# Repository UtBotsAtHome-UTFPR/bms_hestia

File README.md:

# Battery Management System Intelligent (BMSi) 
The BMSi is a open source smart battery management system with the goal of being reliable and affordable with the ability to communicate over USB with robotic systems using ROS or computer with serial terminal, providing all the valuable data needed about the battery.

With the goal of affordability and ease o use the main component is an ESP32, using Arduino Language (C++). The complex part of this project (BQ76942) was simplified with the development of a library, and further development will be done on this to achieve full abstraction on the configuration and use of this IC, making it even more simple to use.

The hardware designs are found under [BMSi-Hardware](https://github.com/MrSerafim/BMSi-Hardware).

Updates require matching firmware and board versions!

### Copyright notice:
Some parts of this software may contain third party libraries and source code licensed under different terms.
The license applying to these files is found in the header of the file.
For all other parts the LICENSE file applies.

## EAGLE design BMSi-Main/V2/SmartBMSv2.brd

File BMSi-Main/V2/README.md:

### BMSi V2 board
This was the first released and working board.

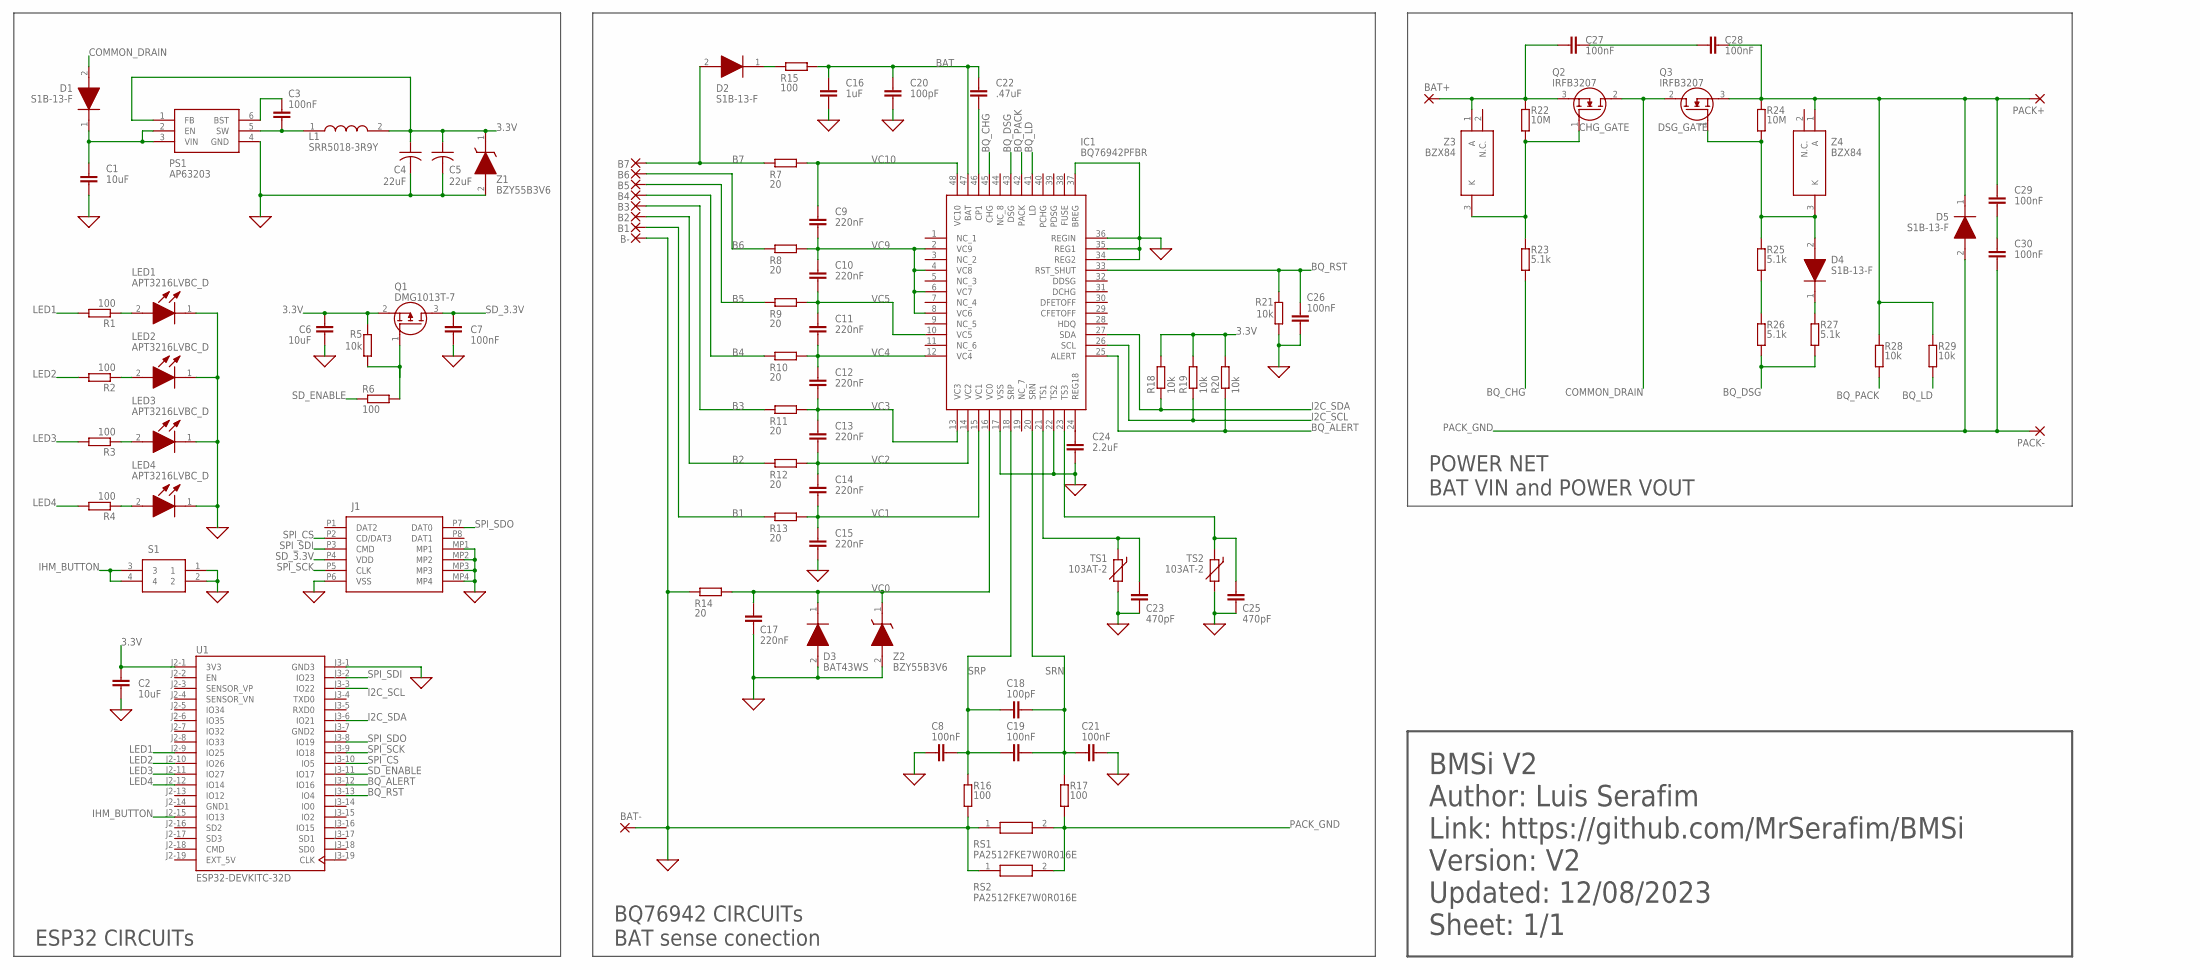
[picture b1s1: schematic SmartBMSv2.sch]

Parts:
B1, B2, B3, B4, B5, B6, B7: SMD5; SMD2,54-5,08
B-: SMD5; SMD2,54-5,08
BAT+: SMD5X10; SMD5-10
BAT-: SMD5X10; SMD5-10
C1, C2, C6: 10uF; C0805
C3, C7, C8, C19, C21, C26, C27, C28, C29, C30: 100nF; C0805
C4, C5: 22uF; C0805
C9, C10, C11, C12, C13, C14, C15, C17: 220nF; C0805
C16: 1uF; C0805
C18, C20: 100pF; C0805
C22: .47uF; C0805
C23, C25: 470pF; C0805
C24: 2.2uF; C0805
D1, D2, D4, D5: S1B-13-F; DIONM5126X230N
D3: BAT43WS; SOD2713X115N
IC1: BQ76942PFBR; QFP50P900X900X120-48N
J1: MEM2067-02-180-00-A; MEM20670218000A
L1: SRR5018-3R9Y; SRR50183R9Y
LED1, LED2, LED3, LED4: APT3216LVBC_D; LEDC3216X95N
PACK+: SMD5X10; SMD5-10
PACK-: SMD5X10; SMD5-10
PS1: AP63203; SOT95P280X100-6N
Q1: DMG1013T-7; SOT50P160X90-3N
Q2, Q3: IRFB3207; TO220_HORIZONTAL
R1, R2, R3, R4, R6, R15, R16, R17: 100; R0805
R5, R18, R19, R20, R21, R28, R29: 10k; R0805
R7, R8, R9, R10, R11, R12, R13, R14: 20; R0805
R22, R24: 10M; R0805
R23, R25, R26, R27: 5.1k; R0805
RS1, RS2: PA2512FKE7W0R016E; RESC6432X88N
S1: FSM2JSMAATR; FSM2J_1
TS1, TS2: 103AT-2; RS-2,5
U1: ESP32-DEVKITC-32D; MODULE_ESP32-DEVKITC-32D
Z1, Z2: BZY55B3V6; DIOC2012X85N
Z3, Z4: BZX84; SOT95P230X110-3N

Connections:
0: B-.1, BAT-.1, C1.2, C2.2, C4.2, C5.2, C6.1, C7.1, C8.1, C15.2, C16.2, C17.2, C20.2, C21.2, C23.2, C24.2, C25.2, C26.2, D3.2 (A), IC1.17 (VSS), IC1.22 (TS2), IC1.34 (REG2), IC1.35 (REG1), IC1.36 (REGIN), IC1.37 (BREG), J1.MP1, J1.MP2, J1.MP3, J1.MP4, J1.P6 (VSS), LED1.1 (K), LED2.1 (K), LED3.1 (K), LED4.1 (K), PS1.4 (GND), R14.1, R16.1, R21.1, RS1.1, RS2.1, S1.1, S1.2, TS1.2, TS2.2, U1.J3-1 (GND3), Z1.2 (A), Z2.2 (A)
3.3V: C2.1, C4.1, C5.1, C6.2, L1.2, PS1.1 (FB), Q1.2 (S), R5.2, R18.2, R19.2, R20.2, U1.J2-1 (3V3), Z1.1 (K)
B1: B1.1, R13.1
B2: B2.1, R12.1
B3: B3.1, R11.1
B4: B4.1, R10.1
B5: B5.1, R9.1
B6: B6.1, R8.1
B7: B7.1, D2.2 (A), R7.1
BAT: C16.1, C20.1, C22.1, IC1.47 (BAT), R15.2
BAT+: BAT+.1, C27.1, Q2.3 (S), R22.2, Z3.1 (A)
BQ_ALERT: IC1.25 (ALERT), R20.1, U1.J3-12 (IO16)
BQ_CHG: IC1.45 (CHG), R23.1
BQ_DSG: IC1.43 (DSG), R26.1, R27.1
BQ_LD: IC1.41 (LD), R29.2
BQ_PACK: IC1.42 (PACK), R28.2
BQ_RST: C26.1, IC1.33 (RST_SHUT), R21.2, U1.J3-13 (IO4)
CHG_GATE: Q2.1 (G), R22.1, R23.2, Z3.3 (K)
COMMON_DRAIN: D1.2 (A), Q2.2 (D), Q3.2 (D)
CP1: C22.2, IC1.46 (CP1)
D2_K: D2.1 (K), R15.1
DSG_DIODE_K: D4.1 (K), R27.2
DSG_GATE: D4.2 (A), Q3.1 (G), R24.1, R25.2, Z4.3 (K)
DSG_RES: R25.1, R26.2
EXT_5V: U1.J2-19 (EXT_5V)
FET_ESDP: C27.2, C28.1
GND1: U1.J2-14 (GND1)
GND2: U1.J3-7 (GND2)
I2C_SCL: IC1.26 (SCL), R19.1, U1.J3-3 (IO22)
I2C_SDA: IC1.27 (SDA), R18.1, U1.J3-6 (IO21)
IHM_BUTTON: S1.3, S1.4, U1.J2-15 (IO13)
LED1: R1.2, U1.J2-9 (IO25)
LED1_ANODE: LED1.2 (A), R1.1
LED2: R2.2, U1.J2-10 (IO26)
LED2_ANODE: LED2.2 (A), R2.1
LED3: R3.2, U1.J2-11 (IO27)
LED3_ANODE: LED3.2 (A), R3.1
LED4: R4.2, U1.J2-12 (IO14)
LED4_ANODE: LED4.2 (A), R4.1
PACK+: C28.2, C29.1, D5.1 (K), PACK+.1, Q3.3 (S), R24.2, R28.1, R29.1, Z4.1 (A)
PACK_ESDP: C29.2, C30.1
PACK_GND: C30.2, D5.2 (A), PACK-.1, R17.1, RS1.2, RS2.2
PS1_BST: C3.2, PS1.6 (BST)
PS1_SW: C3.1, L1.1, PS1.5 (SW)
PS_VIN: C1.1, D1.1 (K), PS1.2 (EN), PS1.3 (VIN)
Q1_GATE: Q1.1 (G), R5.1, R6.2
REG18: C24.1, IC1.24 (REG18)
SD_3.3V: C7.2, J1.P4 (VDD), Q1.3 (D)
SD_ENABLE: R6.1, U1.J3-11 (IO17)
SPI_CS: J1.P2 (CD/DAT3), U1.J3-10 (IO5)
SPI_SCK: J1.P5 (CLK), U1.J3-9 (IO18)
SPI_SDI: J1.P3 (CMD), U1.J3-2 (IO23)
SPI_SDO: J1.P7 (DAT0), U1.J3-8 (IO19)
SRN: C18.2, C19.2, C21.1, IC1.20 (SRN), R17.2
SRP: C8.2, C18.1, C19.1, IC1.18 (SRP), R16.2
TS1: C23.1, IC1.21 (TS1), TS1.1
TS3: C25.1, IC1.23 (TS3), TS2.1
VC0: C17.1, D3.1 (K), IC1.16 (VC0), R14.2, Z2.1 (K)
VC1: C14.2, C15.1, IC1.15 (VC1), R13.2
VC2: C13.2, C14.1, IC1.14 (VC2), R12.2
VC3: C12.2, C13.1, IC1.13 (VC3), R11.2
VC4: C11.2, C12.1, IC1.12 (VC4), R10.2
VC5: C10.2, C11.1, IC1.10 (VC5), R9.2
VC9: C9.2, C10.1, IC1.2 (VC9), IC1.4 (VC8), IC1.6 (VC7), IC1.8 (VC6), R8.2
VC10: C9.1, IC1.48 (VC10), R7.2

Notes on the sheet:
POWER NET BAT VIN and POWER VOUT
BQ76942 CIRCUITs BAT sense conection
ESP32 CIRCUITs
BMSi V2 Author: Luis Serafim Link: https://github.com/MrSerafim/BMSi Version: V2 Updated: 12/08/2023 Sheet: 1/1

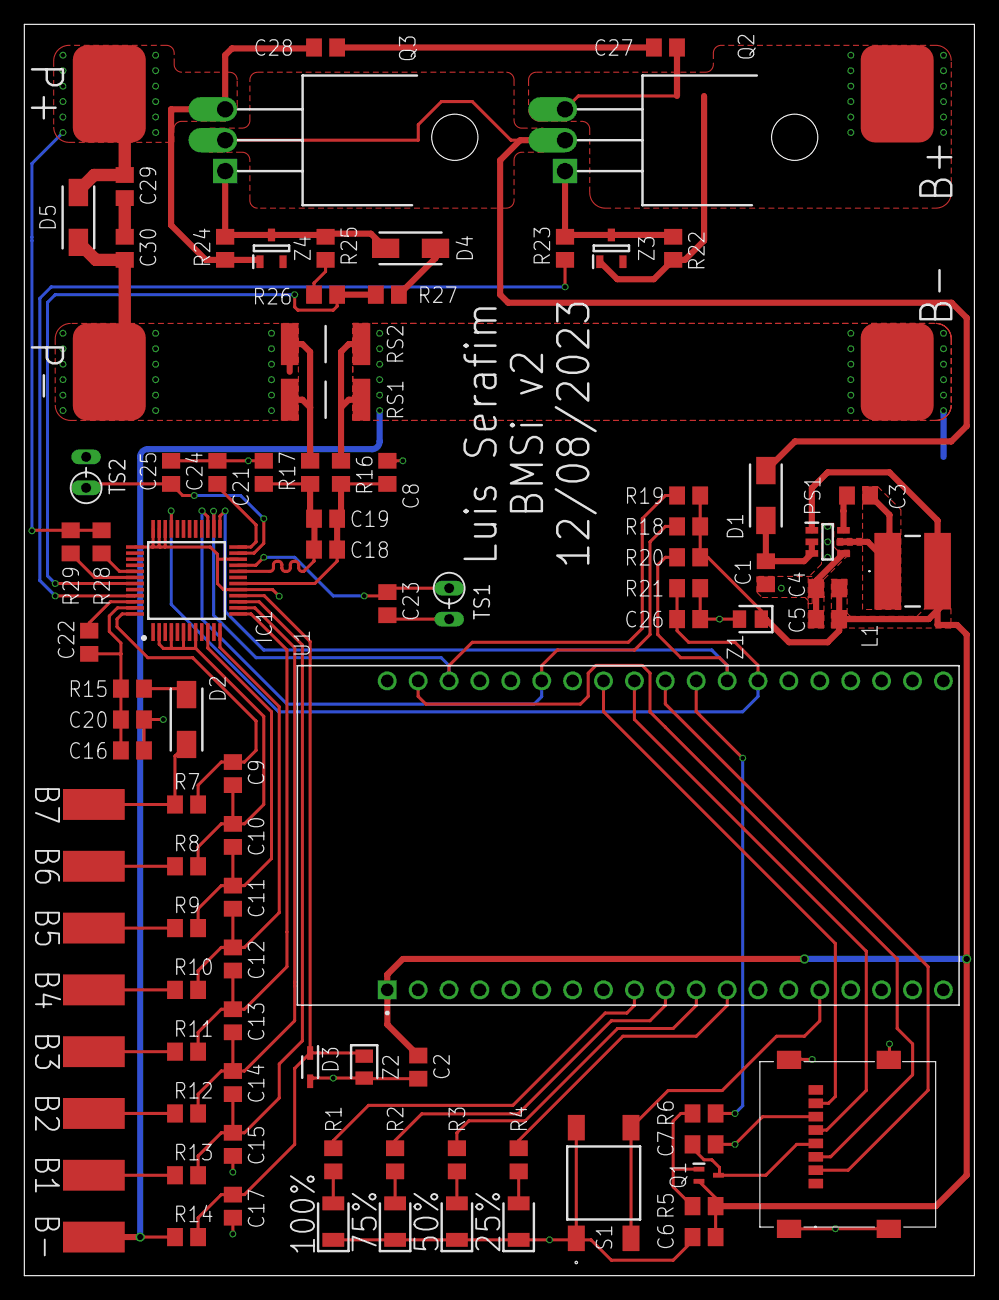
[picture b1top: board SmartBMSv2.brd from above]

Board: 2 copper layers, 78.1 x 102.9 mm, 97 parts (0 on the bottom side), 62 nets.

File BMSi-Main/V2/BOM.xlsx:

PRICE | Qty | TOTAL | Value | Package | Parts | Description | MANUFACTURER_NAME | MOUSER_PART_NUMBER | MOUSER_PRICE-STOCK
2.1000000000000001E-2 | 8 | 0.16800000000000001 | 1/4W 20 OHM 1% | R0805 | R7, R8, R9, R10, R11, R12, R13, R14 | RESISTOR, European symbol |  |  | https://pt.mouser.com/ProductDetail/KOA-Speer/RK73H2ATTD20R0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
2.1000000000000001E-2 | 8 | 0.16800000000000001 | 1/4W 100 Ohms 1% | R0805 | R1, R2, R3, R4, R6, R15, R16, R17 | RESISTOR, European symbol |  |  | https://pt.mouser.com/ProductDetail/KOA-Speer/RK73H2ATTD1000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
2.1000000000000001E-2 | 4 | 8.4000000000000005E-2 | 1/4W 5.1 kOhms 1% | R0805 | R23, R25, R26, R27 | RESISTOR, European symbol |  |  | https://pt.mouser.com/ProductDetail/KOA-Speer/RK73H2ATTD5101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
3.5000000000000003E-2 | 7 | 0.24500000000000002 | 1/4W 10 kOhms 1% | R0805 | R5, R18, R19, R20, R21, R28, R29 | RESISTOR, European symbol |  |  | https://pt.mouser.com/ProductDetail/KOA-Speer/RK73H2ATTDD100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
3.5000000000000003E-2 | 2 | 7.0000000000000007E-2 | 1/4W 10 Mohms 1% | R0805 | R22, R24 | RESISTOR, European symbol |  |  | https://pt.mouser.com/ProductDetail/KOA-Speer/RK73H2ATTDD100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
5.5E-2 | 2 | 0.11 | 100 pF 10% 50V | C0805 | C18, C20 | CAPACITOR, European symbol | Kemet |  | https://pt.mouser.com/ProductDetail/KEMET/C0805C101K5GAC?qs=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
3.4000000000000002E-2 | 2 | 6.8000000000000005E-2 | 470 pF 10% 50V | C0805 | C23, C25 | CAPACITOR, European symbol | Kemet |  | https://pt.mouser.com/ProductDetail/KEMET/C0805C471K5RACTU?q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
2.3E-2 | 10 | 0.22999999999999998 | 100 nF 10% 50V | C0805 | C3, C7, C8, C19, C21, C26, C27, C28, C29, C30 | CAPACITOR, European symbol | Kemet |  | https://pt.mouser.com/ProductDetail/Samsung-Electro-Mechanic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
3.2000000000000001E-2 | 8 | 0.25600000000000001 | 220 nF 10% 50V | C0805 | C9, C10, C11, C12, C13, C14, C15, C17 | CAPACITOR, European symbol | Kemet |  | https://pt.mouser.com/ProductDetail/Samsung-Electro-Mechanic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
5.5E-2 | 1 | 5.5E-2 | 470 nF 10% 50V | C0805 | C22 | CAPACITOR, European symbol | Kemet |  | https://pt.mouser.com/ProductDetail/Samsung-Electro-Mechanic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
7.1999999999999995E-2 | 2 | 0.14399999999999999 | 1 uF 10% 50V | C0805 | C2, C16 | CAPACITOR, European symbol | Kemet |  | https://pt.mouser.com/ProductDetail/Samsung-Electro-Mechanic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
0.14499999999999999 | 1 | 0.14499999999999999 | 2.2 uF 10% 50V | C0805 | C24 | CAPACITOR, European symbol | Kemet |  | https://pt.mouser.com/ProductDetail/Samsung-Electro-Mechanic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
0.26500000000000001 | 2 | 0.53 | 10 uF 10% 50V | C0805 | C1, C6 | CAPACITOR, European symbol | Samsung |  | https://pt.mouser.com/ProductDetail/Samsung-Electro-Mechanic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
0.14299999999999999 | 2 | 0.28599999999999998 | 22 uF 10% 16V | C0805 | C4, C5 | CAPACITOR, American symbol | Samsung |  | https://pt.mouser.com/ProductDetail/Samsung-Electro-Mechanic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
0.80100000000000005 | 1 | 0.80100000000000005 | AP63203WU-7 | SOT95P280X100-6N | PS1 | Switching Voltage Regulators DCDC Conv HV Buck TSOT26 T&R 3K | Diodes Inc. | 621-AP63203WU-7 | https://pt.mouser.com/ProductDetail/621-AP63203WU-7
0.32500000000000001 | 4 | 1.3 | APT3216LVBC_D | LEDC3216X95N | LED1, LED2, LED3, LED4 | Standard LEDs - SMD 3.2X1.6MM LOW CRNT | Kingbright | 604-APT3216LVBCD | https://pt.mouser.com/ProductDetail/604-APT3216LVBCD
0.30599999999999999 | 1 | 0.30599999999999999 | BAT43WS-E3-08 | SOD2713X115N | D3 | Schottky Diodes & Rectifiers 30Volt 200mA 4A IFSM | Vishay | 78-BAT43WS-E3-08 | https://pt.mouser.com/ProductDetail/Vishay-Semiconductors/BA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
0.14399999999999999 | 2 | 0.28799999999999998 | BZX84-C16,215 | SOT95P230X110-3N | Z3, Z4 | Zener Diode 16 V 250 mW +/-5% Surface Mount TO-236AB | Nexperia | 771-BZX84-C16-T/R | https://pt.mouser.com/ProductDetail/771-BZX84-C16-T-R
0.29699999999999999 | 2 | 0.59399999999999997 | BZY55B3V6_RBG | DIOC2012X85N | Z1, Z2 | Zener Diodes 0805 500mW 2% Small Signal Zener Diode | Taiwan Semiconductor | 821-BZY55B3V6RBG | https://pt.mouser.com/ProductDetail/Taiwan-Semiconductor/BZY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
0.189 | 4 | 0.75600000000000001 | S1B-13-F | DIONM5126X230N | D1, D2, D4, D5 | Diodes Inc S1B-13-F Switching Diode, 1A 100V, 2-Pin SMA | Diodes Inc. | 621-S1B-F | https://pt.mouser.com/ProductDetail/Diodes-Incorporated/S1B-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
0.27 | 1 | 0.27 | DMG1013T-7 | SOT50P160X90-3N | Q1 | MOSFET P-Channel 20V 0.46A SOT523 Diodes Inc DMG1013T-7 P-channel MOSFET Transi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 | Diodes Inc. | 621-DMG1013T-7 | https://pt.mouser.com/ProductDetail/621-DMG1013T-7
1.64 | 2 | 3.28 | IRFB3207PBF | TO220_HORIZONTAL | Q2, Q3 | MOSFET MOSFT 75V 180A 4.5mOhm 180nC |  |  | https://pt.mouser.com/ProductDetail/942-IRFB3207PBF
0.56699999999999995 | 2 | 1.1339999999999999 | PA2512FKE7W0R016E | RESC6432X88N | RS1, RS2 | 16 mOhms +/-1% 2W Chip Resistor 2512 (6432 Metric) Anti-Sulfur, Automotive AEC-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 | YAGEO |  | https://pt.mouser.com/ProductDetail/603-PA2512FKE7W0R16E
4.4400000000000004 | 1 | 4.4400000000000004 | BQ76942PFBR | QFP50P900X900X120-48N | IC1 | Battery Management 3-series to 10-series multicell battery monitor and protector | Texas Instruments | 595-BQ76942PFBR | https://pt.mouser.com/ProductDetail/Texas-Instruments/BQ7694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
1.04 | 1 | 1.04 | MEM2067-02-180-00-A | MEM20670218000A | J1 | GCT (GLOBAL CONNECTOR TECHNOLOGY) - MEM2067-02-180-00-A - Memory Socket, MEM206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 | GCT (GLOBAL CONNECTOR TECHNOLOGY) | 640-MEM20670218000A | https://pt.mouser.com/ProductDetail/640-MEM20670218000A
0.28799999999999998 | 1 | 0.28799999999999998 | FSM2JSMAATR | FSM2J_1 | S1 | Tactile switch,SMT,SPST | TE Connectivity | 506-FSM2JSMAATR | https://pt.mouser.com/ProductDetail/506-FSM2JSMAATR
0.35099999999999998 | 1 | 0.35099999999999998 | SRR5018-3R9Y | SRR50183R9Y | L1 | Power Inductors - SMD 3.9uH 30% SMD 5018 | Bourns | 652-SRR5018-3R9Y | https://pt.mouser.com/ProductDetail/652-SRR5018-3R9Y
0.96599999999999997 | 2 | 1.9319999999999999 | 103AT-2 | RS-2,5 | TS1, TS2 | THERMISTOR 103AT-2 10kOhm |  |  | https://pt.mouser.com/ProductDetail/954-103AT-2
9.11 | 1 | 9.11 | ESP32-DEVKITC-32D | ESP32-DEVKITC-32D | U1 | Esp32
Subtotal |  | 28.448999999999998
 |  | 1.59 | PCB JLCPCB
Total |  | 30.038999999999998
Price values updated 12/08/2023

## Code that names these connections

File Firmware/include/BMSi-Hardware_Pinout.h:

/*
 *  BMSi-Hardware_Pinout.h
 *  Created on: nov 30, 2023
 *  Author: Luis Serafim
 *
 * Those are the pins connected of the ESP32 DevKitC V4 on the BMSi-V2 board.
 *
 * The LedIndicator is an OUTPUT that indicate the percentage of battery charge, Led is ON when pin OUTPUT is HIGH.
 * The ButtonIndicator is an INPUT that signals to indicate the battery status, reading LOW when pressed (pulldown button).
 *
 * The SD_power is an OUTPUT that turns on the mosfet to powers the SD card, when LOW the SDcard is ON.
 *
 * The BQ76942_Alert is an INPUT for external interrupt that the BQ76942 pulls down when in the Alert status.
 * The BQ76942_RST is an OUTPUT used to reset the BQ76942 by sending a HIGH signal.
 *
 * The BQ76942 uses I2C protocol with addresses 0x10(Write) and 0x11(Read).
 * The SDcard uses SPI protocol.
 */

#ifndef BMSiV2_H
#define BMSiV2_H

#define LedIndicator_100_Pin 25
#define LedIndicator_75_Pin 26
#define LedIndicator_50_Pin 27
#define LedIndicator_25_Pin 14
#define ButtonIndicator_Pin 13

#define SPI_SDI_Pin 23
#define SPI_SDO_Pin 19
#define SPI_SCK_Pin 18
#define SPI_CS_Pin 5

#define I2C_SDA_Pin 21
#define I2C_SCL_Pin 22

#define SD_Power_Pin 17

#define BQ76942_Alert_Pin 16
#define BQ76942_RST_Pin 4

#endif // BMSiV2

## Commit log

2025-05-13 Revert "Hardware"
